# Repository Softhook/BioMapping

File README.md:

# BioMapping 2

*Christian Nold, 2026*

BioMapping 2 records your Galvanic Skin Response — a measure of emotional arousal — mapped to your geographical location as you walk through an environment. 

It has three parts:

- **[The Hardware](#the-hardware)** — a custom skin-response sensor and a GPS wired to a Flipper Zero.
- **[The Firmware](#the-firmware)** — a C application on the Flipper Zero.
- **[The Visualiser](#the-visualiser)** — browser-based analysis and mapping suite.

## The Original Bio Mapping

The first Bio Mapping device (Christian Nold, 2004) was used in workshops with thousands of people across sixteen countries. Participants walked through an area wearing the device and then annotated the recorded data together, producing collective emotion maps. Results from those workshops are published online — the [Greenwich Emotion Map](http://emotionmap.net/), the [San Francisco Emotion Map](http://www.sf.biomapping.net/) and the [Stockport Emotion Map](http://stockport.emotionmap.net/) — and the approach is discussed in the book [*Emotional Cartography*](http://www.emotionalcartography.net/).

## Bio Mapping 2
Unlike most academic research around Galvanic Skin Response, which is bogged down in jargon and caught in cartesian dualism, this project takes a different path. The goal is a system that is technically rigorous while open for everyday community interpretation. While the old Bio Mapping process was great at getting people involved, it didn't provide the insight into what was happening inside the body and the technical rigour and legitimacy to defend the community data. 

Bio Mapping 2 is a high-fidelity successor that takes you much deeper into the body. It uses more sophisticated hardware and software to track nervous system responses and articulate a new vision of the mind-body. This new version aims to give communities a playful and rigorous tool to explore and tackle real-world issues like local planning, environmental stress, and civic change.

## Quick Start

1. **Build the hardware or talk to me** — gather the [components](#components) and follow the [wiring guide](docs/wiring_guide.md).
2. **Flash the app** — download `biomap.fap` from the [Releases](https://github.com/Softhook/BioMapping/releases) page and copy it to your Flipper's SD card, or build from `firmware/` with [`ufbt`](https://pypi.org/project/ufbt/).
3. **Record a walk** — unplug the device from any charger or computer ([why](#electrode-safety)), launch the Bio Mapping app on the Flipper, clip on the electrodes, and walk. Logs save to `/ext/biomapping/*.csv` on the SD card.
4. **Analyse & map** — drop your CSV into the [online visualiser](https://softhook.github.io/BioMapping/visualiser/) — no install needed.

---

# The Hardware

The device is a Flipper Zero running the Bio Mapping app, wired to a custom skin-response sensor circuit and a GPS module. It records to the Flipper's SD card as CSV.

## What It Records

| Stream | Sensor | Notes |
|---|---|---|
| **Galvanic Skin Response (GSR)** | Transimpedance amplifier + 16-bit ADS1115 ADC | Skin conductance in nanosiemens (nS) |
| **Location** | u-blox SAM-M10Q GNSS | About 1.5 m in open sky (datasheet); worse in streets with tall buildings. Up to 10 Hz (GPS + Galileo + GLONASS + BeiDou) |
| **Environmental RF** | Flipper SubGHz radio | Band activity at 815 / 868 / 915 MHz |

Everything is logged to `/ext/biomapping/*.csv` at 10 Hz. A Live Stream mode sends GPS + GSR over Bluetooth instead of recording.

## Hardware Accuracy & Device Comparison

The GSR front-end is built to research-grade specification and measured against a precision metal-film resistor grid (10 kΩ – 9 MΩ), full sweep in [`docs/gsr_sweeps/reference_test_results5.csv`](docs/gsr_sweeps/reference_test_results5.csv).

Accuracy zones by the fraction of real-world track data that falls inside them:

- **≤ ±0.2%** — 10 kΩ – 1 MΩ (1,000 – 100,000 nS): 99.23% of data
- **≤ ±0.5%** — 10 kΩ – 2.2 MΩ (455 – 100,000 nS): 99.74%
- **≤ ±1.0%** — 10 kΩ – 4.7 MΩ (213 – 100,000 nS): 99.84%
- Below 100 nS (over 10 MΩ) the device reports an open circuit (electrodes disconnected / air).

| Device | Type / Price | ADC Resolution | Noise Floor | Accuracy / Error |
| :--- | :--- | :--- | :--- | :--- |
| [BIOPAC EDA100C + MP160](https://www.biopac.com/product/electrodermal-activity-amplifier/) | Lab Benchmark (~£8,000+) | 16-bit *(MP160 DAQ)* | 0.7 nS *(published sensitivity)* | Unknown |
| **[BioMapping 2](https://github.com/Softhook/BioMapping)** | **Custom Portable (~£250)** | **16-bit** *(Onboard ADS1115)* | **2.7 nS** | **±0.2% *(calibrated)* / ±0.4% *(raw)*** |
| [Empatica E4](https://support.empatica.com/hc/en-us/articles/202581999-E4-wristband-technical-specifications) | Clinical Wearable (~£1,350) *(discontinued)* | Not published *(0.9 nS per step)* | Unknown | Unknown |
| [Empatica EmbracePlus](https://www.empatica.com/embraceplus/) | Clinical Research Wearable (~£1,400+) | Not published *(~0.055 nS per step)* | Unknown | Unknown |
| [Shimmer3 GSR+](https://shimmersensing.com/product/shimmer3-gsr-unit/) | Research Wearable (~£650) | 12-bit *(Onboard MCU ADC)* | Unknown | ±3% to ±10% |
| [Movisens EdaMove 4](https://www.movisens.com/en/products/eda-and-activity-sensor/) | Ambulatory Research (~£800+ est.) | 14-bit | Unknown | Unknown |
| [BITalino EDA](https://www.pluxbiosignals.com/collections/bitalino/products/electrodermal-activity-eda-sensor) | Academic Toolkit (~£200) | 10-bit *(BITalino Core)* | Unknown | Unknown |
| [ProtoCentral tinyGSR](https://protocentral.com/product/protocentral-tinygsr-gsr-eda-digital-output-sensor-board-qwiic-stemma-qt/) | Maker Breakout (~£16) | 12-bit | Unknown | Unknown |
| [Grove GSR v1.2](https://wiki.seeedstudio.com/Grove-GSR_Sensor/) | Hobbyist Module (~£12) | Sensor Only | Unknown | Unknown |

> **Note on comparisons:** Most manufacturers don't publish detailed specifications, and the few that do test in different ways, so the numbers above aren't directly comparable. BioMapping's noise floor and accuracy were measured on the bench against precision resistors. ADC resolution is the figure most often published, and it's a rough guide to how carefully a device was built and what it was built for. Where a maker only gives the size of one measurement step (in nS), that is shown in brackets instead.

## Components

**Core boards**
* **[Flipper Zero](https://flipperzero.one/)**
* **SparkFun u-blox SAM-M10Q GNSS Breakout** — GPS positioning. Integrated 15×15 mm ceramic patch antenna, 10 Hz updates.
* **Flipper Zero Prototyping Board** — mounts the ADS1115 and op-amp circuit.
* **ADS1115 Breakout Board** — 16-bit I²C ADC.

**Active components**
* 1× rail-to-rail dual op-amp (MCP602 / MCP6002 / MCP6042 or equivalent 3.3 V CMOS dual op-amp)

**Passive components** (all 0.1% tolerance metal-film resistors)
* 1× 56 kΩ — voltage divider
* 1× 10 kΩ — voltage divider
* 1× 47 kΩ — TIA gain / feedback
* 2× 4.7 kΩ — electrode safety (inline)
* 2× 100 nF (0.1 µF) ceramic capacitors — one power bypass, one feedback filter

**Biometric interface**
* GSR finger electrodes — biometric finger clips, or velcro strips with foil / copper tape.

## Electrode Safety

Only put the electrodes on someone while the device runs on its own battery. Unplug it from chargers, laptops and anything else connected to the mains first. The two 4.7 kΩ resistors limit the current the device itself can send through the skin, but they can't protect against a faulty or leaky charger, whose current could then reach the skin through the electrodes. Being plugged in also adds mains hum to the readings.

## GSR TransImpedance Circuit

The circuit uses both channels of a rail-to-rail dual op-amp: one as a buffered 0.5 V virtual-ground reference (V_ref), and one as a transimpedance amplifier (TIA) that converts skin current to a voltage read differentially by the ADS1115. Two 4.7 kΩ safety resistors protect the electrodes, and a 100 nF feedback capacitor acts as a hardware low-pass filter against 50/60 Hz mains hum.

Full step-by-step pin connections, op-amp pinout, and build phases are in **[`docs/wiring_guide.md`](docs/wiring_guide.md)**.

---

# The Firmware

The onboard firmware (written in C in `firmware/`) runs as an external application (`biomap.fap`) on the Flipper Zero. It acts as an active signal conditioning and synchronization engine, managing the ADC, the GPS module, and the SubGHz radio concurrently.

## What the Firmware Does

- **Real-Time Dynamic Auto-Ranging:** Human skin conductance spans several orders of magnitude across individuals and resting states (from under 500 nS to tens of thousands of nS). The firmware steps the ADS1115's Programmable Gain Amplifier (PGA) across four voltage ranges (from ±2.048 V down to ±0.256 V). A 4 ms settle-gate discards conversion transients during gain switches, and readings from every range are normalised to one common scale, so the output is continuous across gain changes (see the [calibrated wide-range error curve](#hardware-accuracy--device-comparison)).
Looking at other open-source and maker EDA devices whose firmware is available to inspect, almost none implement auto-ranging in firmware.

- **50/60 Hz Mains Hum Rejection:** Ambulatory electrodes pick up AC mains hum from power lines. The ADC uses a background thread to compute a 100 ms boxcar average to null 50 Hz, 60 Hz, and their harmonics (100 Hz, 120 Hz).
- **Multi-Sensor Synchronisation:**  Parses 10 Hz GNSS sentences from the u-blox SAM-M10Q over UART, paces SubGHz RF RSSI snapshots across 815/868/915 MHz without blocking biometric sampling, and streams over Bluetooth or writes to SD.

## Installing the App

A Flipper external app (FAP) for stock firmware; also runs on the API-compatible forks (Momentum, Unleashed, RogueMaster). Download `biomap.fap` from the [Releases](https://github.com/Softhook/BioMapping/releases) page, or build from `firmware/` with [`ufbt`](https://pypi.org/project/ufbt/).

Run the host unit tests with `./run_tests.sh` from `firmware/`.

## CSV Schema

[`docs/csv_schema.md`](docs/csv_schema.md) is the canonical, versioned definition of every column and sentinel value, shared by the device and both visualiser pages.

---

# The Visualiser

The visualiser runs client-side in any modern browser with no server, installation, or build step required. You can launch it directly online:

👉 **[Launch BioMapping Visualiser Online](https://softhook.github.io/BioMapping/visualiser/)**

It provides two entry points:

- **Track Visualiser & Analysis** ([Online App](https://softhook.github.io/BioMapping/visualiser/) | [`visualiser/index.html`](visualiser/index.html)) — Load recorded `.csv` logs from the device to inspect waveforms, clean signals, detect SCR events, map emotional arousal in 2D or 3D, and generate collective emotion maps across participants.
- **Live Stream Visualiser** ([Online Live View](https://softhook.github.io/BioMapping/visualiser/live.html) | [`visualiser/live.html`](visualiser/live.html)) — Connects to the Flipper Zero in real time via Web Bluetooth to graph live biometric arousal and plot GPS movements as you walk. The same view is also built into the main app as the **Live** tab, next to Single and Collective.

## Available Methods & Pipeline

The visualiser provides a full suite of research-grade methods for ambulatory EDA signal processing and spatial analysis:

- **Signal Filtering & Motion Artefact Rejection:**
  - *Hampel / Median Filter* — Removes transient spikes and electrode loose-contact glitches.
  - *Butterworth Low-Pass* — 4th-order zero-phase filter to smooth high-frequency electrical fuzz and tremor.
  - *Zero-Phase Gait Filter* — 4th-order Linkwitz-Riley low-pass at 1.0 Hz, tuned to reject ~1.4–2.0 Hz walking-cadence ripple without ringing or genuine SCR amplitude loss.
- **Tonic / Phasic Decomposition:**
  - *Ultra Low-Pass (EMA)* — Exponential moving average baseline estimation with configurable time window (15–90 s).
  - *Moving Median* — Robust sliding-window baseline estimation.
  - *Trough Tracker* — 10th-percentile baseline follower.
  - *Matching Pursuit Deconvolution* — Greedy decomposition against a canonical Bateman SCRF kernel.
  - *SparsEDA* — Sparse deconvolution using multi-scale dictionary pursuit and active-set refinement.
  - *cvxEDA* — Convex optimisation jointly estimating cubic B-spline tonic drift and physiological sudomotor nerve impulses.
- **Peak Detection (SCR):**
  - *Full-Scan Trough-to-Peak (Default)* — Evaluates candidate peaks against minimum amplitude, SNR, and shape-quality criteria.
  - *Topographic Prominence* — Measures peak height relative to adjacent troughs, isolating compound responses riding larger rises.
  - *Driver Impulses* — Direct peak extraction from deconvolution and cvxEDA sudomotor nerve drivers.
- **Autonomic Indices & Derived Metrics:**
  - *Tonic SCL & Phasic SCR* — Separates slow baseline level from rapid emotional responses.
  - *Peak Density & Phasic AUC* — SCR frequency over time and cumulative phasic energy (Area Under the Curve).
  - *Arousal Index & Tri-Index* — Normalised multi-parameter arousal intensity metrics.
  - *EDASymp* — Spectral sympathetic tone index derived from low-frequency EDA dynamics.
- **Spatial & Collective Mapping:**
  - *Pedestrian GPS Filter Pipeline* — HDOP and fix-type gating, a constant-velocity Kalman filter with a Rauch-Tung-Striebel smoother (holding position while you stand still), optional road snapping, and smooth 10 Hz path reconstruction between fixes. Details in [`docs/gps_filtering_pipeline.md`](docs/gps_filtering_pipeline.md).
  - *Dual 2D/3D Rendering* — Toggle between interactive 2D maps and 3D globe terrain.
  - *Multi-Metric Path Colouring* — Dynamically colour paths by raw GSR, phasic arousal, tonic level, peak density, or RF field activity.
  - *Spatial Hotspots & "Places"* — Spatial clustering of emotional arousal sites along walking routes.
  - *Collective Emotion Topography* — Multi-track aggregation generating shared contour surfaces and arousal isolines across groups of participants.
  - *Environmental Layers* — Overlaid OpenStreetMap geometries (buildings, parks, water), Sentinel-2 NDVI satellite vegetation greenness, and tri-band RF fluid fields.

## Software & Algorithmic Accuracy

Detecting a genuine skin-conductance response (SCR) — separating it from sensor noise, walking motion, and baseline drift — is a well-studied problem in psychophysiology, with two established open-source reference tools: **NeuroKit2** (Python) and **Ledalab** (MATLAB/Octave), plus the peer-reviewed **cvxEDA** convex-optimisation model for decomposing skin conductance into its slow (tonic) and fast (phasic) components.

BioMapping ships its own detection pipeline — built to run entirely client-side, in the browser, on recordings made while walking outdoors — and checks it against those references on three grounds:

1. **A synthetic benchmark with a known answer.** Generated tracks carry SCR events at exactly known times and amplitudes, across a range of difficulty (evenly spaced, densely packed, overlapping bursts, and walking motion), so detection accuracy can be measured directly rather than inferred.
2. **Direct agreement on real recordings.** On clean, stationary recordings — the condition NeuroKit2 and Ledalab are designed for — BioMapping's output is compared peak-for-peak against theirs.
3. **A 62-track real-world field corpus.** Outdoor walking recordings totalling over 100,000 data points, to confirm the above holds up outside the lab.

**On the known-answer synthetic benchmark** (210 injected responses, evenly spaced through overlapping and compound), BioMapping's detectors sit at the strong end of recall, precision, and timing accuracy:

| Detector | Recall | Precision | F1 | Mean timing error |
|---|---:|---:|---:|---:|
| **BioMapping Full-Scan** (production default) | 93.3% | 100.0% | 0.966 | 0.029 s |
| **BioMapping Prominence** | 95.2% | 99.5% | 0.973 | 0.032 s |
| NeuroKit2 (default) | 83.8% | 84.2% | 0.840 | 0.035 s |
| Ledalab CDA (literature-tuned) | 81.9% | 88.2% | 0.849 | 0.556 s |

**On real, clean stationary recordings**, agreement with NeuroKit2 is close to total — BioMapping's Prominence detector matches 100% of NeuroKit2's own peaks (163/163) within ~60 ms, while also picking up dozens of genuine subtle responses NeuroKit2's fixed relative threshold leaves out.

**The standout result is cvxEDA.** BioMapping's from-scratch JavaScript port of the convex-optimisation solver reproduces the published Python reference implementation's output essentially exactly — on the full 62-track field corpus, 99.7% of 4,494 detections matched with a mean timing difference of 0.002 seconds — entirely in-browser, with no Python, MATLAB, or server backend required.

**Where BioMapping is built differently** is ambulatory use: NeuroKit2 and Ledalab are designed for seated laboratory sessions, so BioMapping adds a zero-phase motion filter tuned to footstep cadence and a noise-floor gate for sensor dropouts, neither of which a stationary-recording toolbox needs. On a synthetic walking benchmark with the gait filter enabled, BioMapping recovers 100% of injected responses at 96.8% precision.

 Methodology is in [`docs/eda_benchmark.md`](docs/eda_benchmark.md).

---

# Contributing

Bug reports, hardware build notes, and pull requests are welcome. A few things to know before you submit:

**Firmware (C — `firmware/`)**
- Run the host tests before opening a PR: `./run_tests.sh` from the `firmware/` directory.
- Each device has its own firmware version number: `fap_version` in `firmware/application.fam` (Flipper) and `custom_firmware_version` in `firmware/cardputer/platformio.ini` (Cardputer). Raise it for each release. Every recording's `# Firmware` line carries it, with the git commit it was built from (see [`docs/csv_schema.md`](docs/csv_schema.md)).
- The app targets the Flipper Zero SDK via [`ufbt`](https://pypi.org/project/ufbt/); keep changes compatible with stock firmware and the API-compatible forks (Momentum, Unleashed, RogueMaster).

**Visualiser (JavaScript — `visualiser/`)**
- The app is plain ES modules with no build step. Run `npm ci` once to install dev tools, then:
  - `npm test` — Node test runner
  - `npm run lint` — [Biome](https://biomejs.dev/) linter (also runs on every PR via CI)
  - `npm run lint:deps` — checks module dependencies with [dependency-cruiser](https://github.com/sverweij/dependency-cruiser) (e.g. no circular imports)
  - `npm run typecheck` — [TypeScript](https://www.typescriptlang.org/) checks the JavaScript against its JSDoc comments (`@param`, `@returns`, `@typedef`). Nothing is compiled; the shared data shapes are in `visualiser/types/`
  - `npm run format` — auto-format with Biome
  - `npm run check` — lint, dependency check, type check and tests in one go
- CI runs lint, the dependency check, the type check and tests automatically on every push to `main` and on every pull request.
- Run `git config core.hooksPath .githooks` once per clone to enable a pre-commit hook that auto-formats/lints staged visualiser files with Biome, so CI's lint step doesn't fail on something that could have been caught locally.

**Docs & CSV Schema**
- [`docs/csv_schema.md`](docs/csv_schema.md) is the canonical schema shared by the firmware and both visualiser pages — update it whenever the CSV format changes.
- New `docs/` files for proposals or research notes are welcome.

Open an issue first if you're planning a significant change — especially to the sensor circuit, the signal processing pipeline, or the CSV schema — so we can discuss it before you invest the time.

---

# Licence

Bio Mapping is open for community, artistic, and educational use under the **Bio Mapping Community Licence 1.0**.

In short: You are free to build your own Bio Mapping devices for personal use, research, and workshops (including charging participants for materials). You cannot manufacture or sell Bio Mapping hardware or software commercially without written permission. See [LICENCE.md](LICENCE.md) for full details.

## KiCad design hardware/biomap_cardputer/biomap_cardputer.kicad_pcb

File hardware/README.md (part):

# BioMapping circuit boards (KiCad)

**The focus is the Cardputer board.** All current work goes into it. The Flipper board is not the goal right now and is not being worked on: it is kept, it still builds and passes its checks, but it is not being improved or tested, and it doesn't get the Cardputer board's improvements (for example its C9 is still ceramic, and its GPS pads have no wider solder mask).

Two KiCad 10 projects. Both carry the same GSR circuit as [docs/wiring_guide.md](../docs/wiring_guide.md) and the u-blox SAM-M10Q GPS module, soldered straight onto the board (no breakout board):

| Folder | Plugs into | Board | Power |
|---|---|---|---|
| `biomap_cardputer/` (**the focus**) | A short cable inside the Cardputer, soldered to the EXT socket's legs | 79.8 × 49.8 mm, inside a printed back case ([case/](case/)) | Own 3.3 V regulator (TLV75533), fed from EXT 5 V out |
| `biomap_flipper/` (not being worked on) | Flipper Zero GPIO | 72 × 52 mm, stands up from the Flipper's top edge | Flipper's 3.3 V (pin 9) |

Both boards are placed and routed. KiCad's checks pass on both: the wiring check (ERC) and the design rules check (DRC) show 0 errors and 0 warnings, nothing is unconnected, and each board matches its schematic.

## How the schematic is drawn

Each schematic is one A3 sheet split into labelled blocks:

1. Skin sensor (current-to-voltage amplifier)
2. 0.5 V reference and op-amp supply
3. Analogue-to-digital converter
4. Header (Flipper) or cable socket (Cardputer)
5. GPS
6. 5 V to 3.3 V regulator (Cardputer only)

Inside a block, parts are joined by drawn wires. Between blocks, a signal is carried by a name tag (a "net label"), for example `GSR_SIGNAL` or `I2C_SDA`: every tag with the same name is the same wire. 3.3 V and GND use the usual power symbols.

## How the boards are laid out

Each board has two halves.

- **GSR half.** The parts follow the signal: cuffs, then R3/R4, then the op-amp, then the ADC. The cuff socket sits at the board edge with its opening 0.75 mm inside it, so nothing sticks out past the edge and the plug can be pushed in and pulled out straight, with fingers free to grip it. The amplifier's input wire, which carries the tiny skin current and is the most sensitive to noise, is under 10 mm long (about 7 mm on the Cardputer). Each 100 nF supply capacitor sits close to the power pin of its chip: C1 and C3 about 2 mm (each right beside the pin), C7 about 3.7 mm on the Flipper and 2.5 mm on the Cardputer (bridging the GPS supply pad and the ground pad next to it). The ground ends of C1 and C3 reach ground through a via right beside the capacitor, and the chips' ground pins have their own via within 1.6 mm, so each loop is about 2.3–2.7 mm in all (see `./pcb measure`).
- **0.5 V guard.** A patch of copper held at 0.5 V surrounds the amplifier's input wire, R4, C2, R5 and the cuff-2 wire. That wiring also sits at about 0.5 V, so no current can leak between it and the guard. Without the guard, ground copper 0.3 mm away could leak a little current through flux left on the board, and that current would be added to the skin reading. The flux can't simply be washed off, because the GPS module mustn't be washed. The guard joins the reference at U1 pin 3, right beside the input pin 2. Ground copper is kept out of the guard's area: even U1's own ground pin takes its via just outside it.
- **Test pads.** TP3 (GSR output), TP5 (ground) beside it, and TP4 (0.5 V reference), for a meter or scope when checking a new board. A meter between TP3 and TP4 reads exactly what the ADC reads, so it checks the amplifier without trusting the ADC or the firmware. Expect about 0.50 V from TP4 to TP5. From TP3 to TP4, expect about 0 V with the cuffs unplugged, 0.417 V with 47k in the cuff socket, 0.215 V with 100k and 0.049 V with 470k. A scope on TP3 shows hum before the ADC and the firmware's averaging smooth it. A scope on mains power joins the board to earth, which can change the hum itself; a battery scope doesn't.
- **The test pads can't calibrate the board.** The reading compares the GSR output with the 0.5 V, and the same ADC measures both, so any error in the ADC's own scale cancels out. What sets the accuracy is R5, R3 + R4 and the zero, and the pads come after R3 and R4. The calibration wizard, with resistors in the cuff socket, tests the whole path. If a wizard result looks odd, TP3 shows whether the amplifier or the ADC is off.
- **GPS half.** The module sits in the middle of an unbroken ground area of about 50 × 52 mm (Flipper) or 48 × 50 mm (Cardputer). Small parts sit right beside the pins they serve. C7 bridges the module's supply pin and the ground pin next to it. On the Cardputer the module is turned so its serial pins face up towards the cable socket, its supply pin (VCC) faces the regulator, and its second supply pin (V_IO) and backup pin face the empty space below it. There C6 (10 µF) bridges V_IO and the ground pin next to it, and C8 does the same for the backup pin. The backup cell sits just below the module, beside its charger (D1, R8). Each serial resistor sits at the end that drives its wire: R10 at the GPS (TX), R9 at the cable socket (RX).

On the Flipper, long runs (I2C and the 3.3 V feed) go along the board edge on the other copper layer, outside the GPS area. The Cardputer needs almost none: the cable socket's pins step through to the outer face, and every other track is on it (see "How the Cardputer board is laid out" below). Ground fills both copper layers, joined by a grid of vias: 3 mm apart around the GPS, 5 mm elsewhere, and 2 mm apart under the Cardputer's GPS module. KiCad has a "GPS keep clear" zone that refuses new traces under and around the module, so hand edits can't break this by accident.

## The GPS ground plane

The SAM-M10Q's antenna uses the board's ground as part of the antenna. u-blox's integration manual (in `docs/datasheets/`) asks for:

- a solid ground plane of 50 × 50 mm, with the module in the middle; performance drops a lot below 40 × 40 mm
- no signal traces under the module, and ground vias filling the plane under it
- nothing taller than 3 mm within 10 mm of the module
- a plastic case at least 5 mm from the antenna

SparkFun's breakout is 40.6 × 40.6 mm, the minimum, with ground on both layers and about 100 vias. These boards give the module a larger ground area. The module's own circuit copies SparkFun's:

- 100 nF on the supply (plus a 10 µF reservoir, which SparkFun doesn't have)
- a rechargeable backup cell (BT1, Seiko MS421R, the same cell SparkFun uses), charged through D1 and a 3.3 kΩ resistor (Seiko asks for at least 3 kΩ when charging from 3.3 V), with a capacitor (C8) on the backup pin
- 470 Ω in series with TX and RX

C8 is 100 nF on the Flipper, as on SparkFun's board, and 1 µF on the Cardputer. When the power goes off, the module switches its backup pin over to the cell and draws a short burst of current. u-blox warns that a high resistance on that pin makes the voltage dip. The cell's own resistance is about 600 Ω, so the bigger capacitor gives that burst more to draw on.

On the Cardputer, the solder mask round the module's pads opens 0.05 mm wider than each pad, as in u-blox's footprint drawing. A slightly misplaced mask then can't cover a pad edge, which under the module can't be seen or reached. The Flipper board still has the mask flush with its pads.

Two test pads, SAFEBOOT/PPS and RESET, take the place of SparkFun's header pins. Each has a ground pad 1.2 mm from it (TP6, TP7), so tweezers can bridge the pair and a scope's ground has somewhere to go. Each pad's name is printed beside it. The firmware needs no change: it uses the same serial pins as before.

- **TP1, SAFEBOOT/PPS.** Inside the module, the SAFEBOOT pin is joined to the time pulse output through 1 kΩ (u-blox integration manual, section 3.2.3). The firmware leaves the time pulse at u-blox's default, so once the GPS knows the time, this pad goes high for 0.1 s at the start of every second ("PPS", pulse per second). Before that, and while the GPS sleeps, it stays low. On a scope you see the pulse; on a meter the number jumps once a second. So it shows the GPS has the time without looking at either screen, and it marks the true start of each second for timing tests. Held to ground (TP6) while the GPS powers up, it starts the GPS in safeboot mode. That is almost never needed, because this GPS's own program is fixed in the chip. It also means nothing may pull this pad low at power-up, an LED to ground for example: the GPS would start in safeboot mode and seem dead. A meter or a scope is fine.
- **TP2, RESET.** Bridged to TP7, it resets the GPS. That clears the GPS's stored data, so the next fix is a cold start. It is rarely needed: Options > Cold Reset GPS wipes the same stored data over the serial line, and the firmware never saves settings into the GPS, so turning the power off and on clears any bad setting. It is for a GPS that stops answering even then.
- On the Cardputer these pads face outwards. A metal object lying across a pair would reset the GPS, or start it in safeboot mode at power-up: one more reason to keep metal off this side.

## Parts

- **ADS1115 as a bare chip** (MSOP-10). Both boards have their own I2C pull-up resistors (R6, R7, 4.7 kΩ to the board's 3.3 V). On the Cardputer the ADC has an I2C bus of its own (G3 and G5), and the Cardputer has no pull-ups on those pins.
- **Precision resistors suggested** for R1, R2 and R5 (0.1%), and a **C0G capacitor** for C2. These set the GSR scale directly. R3 and R4, the two 4.7k skin current limiters, are 0.1% too: the firmware subtracts exactly 9.4k for them, and with 1% parts that sum could be up to 94 Ω out, enough to read very sweaty skin (around 10k) up to about 1% low.
- **Op-amp: TI OPA2333AIDR** (U1), a "zero-drift" op-amp. Its input error is under 10 µV, against up to 4.5 mV for the MCP6002 on the hand-built prototype, so the 0.5 V across the skin stays exact and doesn't drift with temperature. It has the same pins as the MCP6002. Buy TI's own part: LCSC also lists cheaper copies from other makers with different specs.
- **C9 (10 µF) across R2** smooths the 0.5 V bias. The bias is taken from 3.3 V, and the GSR reading scales with it, so without C9 any wobble on 3.3 V would show up in the reading. On the Cardputer board C9 is a **tantalum** part (Kyocera AVX TAJP106M010RNJ), with its + end (marked on the board) towards the 0.5 V. Ordinary ceramic capacitors turn knocks into tiny voltages, and anything added to the 0.5 V shows up in the GSR reading; in the case, C9 sits right behind the keyboard and the speaker. Its tiny leakage shifts the 0.5 V very slightly, which the bias check at the start of each recording measures away. The Flipper board's C9 is still ceramic.

Each board's `bom.csv` lists every part with its maker, maker's part number and LCSC number (LCSC is the parts store JLCPCB assembles from). Identical parts share one row. The everyday resistors and capacitors are JLCPCB "basic" parts, which have no extra fitting fee.

Everything is surface-mount and suits machine assembly, except the angled pin headers, and the Cardputer's cable socket, which is on the other face and soldered by hand.

- **Finger cuffs:** JST PH 2-pin side-entry socket, surface-mount (J2, S2B-PH-SM4-TB). Its two side tabs only hold it down. The cuff plug was measured on the prototype's top-entry socket (6 mm wide, pins 2.0 mm apart), so it is JST PH and fits; it is held by the same friction bump in a side-entry socket. JST PH is a common series: spares are easy to buy (LCSC C295747, Digi-Key, Mouser, Farnell), and it is easy to solder by hand (tack one tab, then the two pins, then the other tab).
- **GPS:** u-blox SAM-M10Q-00B (U4), on KiCad's standard SAM-M8Q footprint; u-blox says the two modules are pin-compatible. **LCSC has none in stock**, so buy them from Mouser or Digi-Key and send them to the assembler.
- **Backup cell:** Seiko MS421R-IV03E (rechargeable, 3 V, 1.5 mAh, 4.8 mm). It can go through the soldering oven, so a machine fits it like any other part. It is the cell on SparkFun's SAM-M10Q board, and its footprint (`BioMap.pretty/Seiko_MS421R_IV03E`) copies SparkFun's pads. Those pads match the IV03E terminal drawing on Seiko's MS421R page, with about 0.3 mm to spare: the small corner tab is + (pad 1), the long tab is −. Seiko rates the cell for 3 µA in normal use and 10 µA at most, but with the GPS switched off the module draws 28 µA from it. That doesn't harm the cell, but it gets less of its stored charge out, so expect it to keep satellite data for about a day at most. After a longer time off, the GPS takes longer to find its first position. Not stocked by LCSC; Farnell 3534555.
- **C2** is 1206 size, because 100 nF C0G capacitors are hard to find in 0805.
- **Flipper header:** two angled through-hole pieces, pins 1–8 and 9–18, 17.78 mm apart, to match the gap in the Flipper's GPIO. Through-hole is kept on purpose: these joints hold the board in place.
- **Cardputer connection:** a JST GH 8-pin socket (J1, SM08B-GHS-TB: 1.25 mm pitch, latching, side entry, 4.25 mm tall) on the board's inner face, for a short cable soldered inside the Cardputer (see below). LCSC C265111 (a JLCPCB "extended" part); it is soldered by hand, so it isn't in the factory parts list.

## How the Cardputer board is laid out

Seen from the outside, the GSR circuit is on the left half and the GPS on the right. (In KiCad, which shows the board from the Cardputer's side, it is the other way round.) The board sits inside the printed back case ([case/](case/)), where M5Stack's floor used to be, so it is 2.1 mm smaller than the Cardputer all round. It has the Cardputer's big rounded corners on the EXT edge and smaller rounded corners on the keyboard edge. It has four holes. The case's two long screw posts pass through the big ones (H3, H4), where M5Stack's back screws in, and the board rests on their ledges. Two M2 screws (H1, H2) hold it on two shorter posts.

The cable socket J1 sits on the inner face near the EXT edge, on the GSR side, with its mouth facing into the board. Each of its eight pins drops through a via to the outer face: those 1.6 mm steps are the only tracks on the inner face. From the GPS end, the pins carry the two GPS serial wires, ground, 5 V, SDA, SCL, ground and the ADC's ready line.

- The GPS pair runs left along the top edge, then down to the top of the module as a parallel 45-degree pair, with ground vias between them.
- 5 V runs left under it to the regulator, which sits above the GPS. The regulator's 3.3 V goes out in two branches: down to the GPS, and a spine down the left of the GSR circuit, passing left of the screw post.
- The I2C pair and the ready line go straight down on the other side of the post. The I2C pair turns along the gap between the post and the ADC, then comes down the ADC's left side, where the pull-ups R6 and R7 lie across from the spine. On the way down, both wires step sideways by one resistor's width. So R6 reaches SDA above the step, and R7 reaches SCL below it, with SDA passing between R7's pads.

So no wire crosses another.

The GSR circuit is one block, with the cuff socket on the far short edge from the GPS, its opening 0.75 mm inside the board's edge, behind a window in the case wall. The ADC sits just above the op-amp. The op-amp's output and the 0.5 V reference run straight up to it, side by side, with test pads TP4 (0.5 V) and TP3 (GSR output) on them and TP5 (ground) beside them. The test pads have no printed names, because there is no room: from the GPS side they are 0.5 V, GSR output, ground.

**The ADC's ready line.** The ADS1115's ALERT/RDY pin goes to the cable socket's pin 8, for a wire to EXT pin 3 (G4). That wire isn't fitted yet: G4 is in the middle of the hidden row of legs, and the firmware doesn't use it. With it, the ADC could pulse the line each time a new reading is ready, so the firmware could read exactly 860 readings a second, with none missed and none read twice (see `docs/cardputer_port.md`, "GSR reading speed"). The pin can only pull the line low, so it needs a pull-up resistor. The board has none: the firmware would turn on the ESP32's own pull-up on G4, and switch the ADC's ready mode on (set the top bit of the high threshold register and clear it in the low one). Test pad TP8 (printed RDY) sits on the ready line above the ADC, for a scope or logic analyser, with TP5 as its ground.

## How the Cardputer connects

The board sits in a printed back case that replaces M5Stack's back ([case/README.md](case/README.md)). A short cable joins it to the Cardputer. At one end, its wires are soldered inside the Cardputer onto the legs of the EXT socket. At the other, its plug latches into J1 on the board's inner face. J1 sits in the strip between the EXT edge and the battery, where M5Stack's back had its Lego tubes, so nothing of the Cardputer's comes down that far. Its mouth faces into the board, away from the EXT socket's body, so the plug lies over flat board.

| J1 pin | Signal | EXT leg |
|---|---|---|
| 1 | GPS to Cardputer | G15 |
| 2 | Cardputer to GPS | G13 |
| 3 | Ground | GND |
| 4 | 5 V | 5VO |
| 5 | ADC data (SDA) | G5 |
| 6 | ADC clock (SCL) | G3 |
| 7 | Ground | GND (the same leg) |
| 8 | ADC ready | G4 (no wire yet) |

The pins and their legs are printed on the inner face beside the socket. The inner face also carries `Bio Mapping 2 - Cardputer rev G` (bottom left) and `www.biomapping.net` (bottom right), placed like the credit line and the GPS note on the outer face (JLCPCB prints both faces at no extra cost). The revision letter is set once, as `REV` in `pcbtools/boards/cardputer.py`, and feeds both faces: change it whenever the board changes. The case README explains the soldering inside the Cardputer and the checks before switching on. **5VI must never be connected.**

The firmware uses the same pins (`GSR_SDA_PIN` and `GSR_SCL_PIN` in `firmware/cardputer/src/gsr_cardputer.cpp`). A prototype wired with flywires must follow the board: ADC clock on G3, not G6.

## Check before ordering (both boards)

- **Soldering the GPS module.** Its pads sit underneath it, so it needs an oven or a hotplate. u-blox advises against a hot air gun, which can overheat and damage the module. Follow u-blox's soldering profile and use no-clean flux. Don't wash the board afterwards with water, alcohol or an ultrasonic cleaner; the manual warns that each one can damage the module.
- **Oven limits to give the factory.** You send the GPS modules and backup cells to the factory yourself, so send these limits with them. Every part sits on one face, so one pass through the oven is all the board needs.
  - GPS: one pass only, module facing up, at most 245 °C, with 40–60 s above 217 °C (u-blox integration manual, section 5.3).
  - GPS: keep it in its sealed bag until it is fitted. It soaks up damp from the air (moisture level 4). After about 72 hours out of the bag it has to be baked dry first, or it can crack inside in the oven.
  - Backup cell: two oven passes at most, with the temperature measured on top of the cell (Seiko's catalogue).
- **Which way the antenna faces.** The antenna works best facing the sky. On the Flipper, the board stands up from the top edge, so the antenna faces sideways while the Flipper lies flat and faces up when the Flipper is held upright. On the Cardputer, it faces out from the back.

## Check before ordering (Cardputer)

These come from M5Stack's 3D model and from photos, not from measurements of a real device. `./pcb case` checks the board against the case in 3D (see the case README), and `./pcb print` makes a full-size paper copy to lay on the opened Cardputer (see "Paper fit test" below).

- **Room for the cable socket.** J1 stands 4.25 mm up from the board's inner face, into the strip between the EXT edge and the battery. M5Stack's Lego tubes and add-on screw slots filled that space to within 1 mm of the Cardputer's board, so nothing there should stand taller than 1 mm. Check it on the real Cardputer (case README, measurement 2). With the paper copy laid on, J1 must sit over flat board, clear of the EXT socket's body, the headphone socket and the flat-cable socket beside it.
- **Room for the screw heads.** The heads of the board's two M2 screws (H1, H2) are on the inner face, 1.6 mm tall. Nothing under them on the Cardputer's board may stand taller than about 4.5 mm.
- **The long screws.** Measure M5Stack's back screws first (case README, measurement 1). The case's screw length, and how far each screw reaches into the Cardputer, are settings in `case/cardputer_back.scad`.
- **The ADC clock on G3.** Test 1 in the case README checks it on the prototype.

## Paper fit test (Cardputer)

`./pcb print` writes `out/biomap_cardputer_print.pdf`: the board at full size on one A4 page, seen from outside, inside the Cardputer's own outline.

- Print it at 100% ("Actual size"), not "Fit to page", then measure the two 100 mm rulers on the page. Printers are often slightly off, so check before trusting the fit.
- Cut along the outer line (the Cardputer's outline) and lay it on the opened Cardputer, EXT edge to EXT edge. The two big + marks must sit over the two screw inserts.
- J1 and its pads are on the hidden face, so they are drawn as seen through the paper. They must sit over flat board.
- KiCad draws the page from the board files, so it always matches the current layout. Tracks and copper fill are left out to save ink.

## Factory files

The ways of getting the boards made (UK assembler, JLCPCB, or by hand) and rough costs are in [BUILD_COSTS.md](BUILD_COSTS.md).

`./pcb fab` (or `./pcb fab cardputer`) first runs every check that `./pcb check` runs. If any fails, it writes nothing. Otherwise it fills a folder `out/fab/<board>/` for each board:

| File | What it's for |
|---|---|
| `<board>_gerbers.zip` | Upload this to have the bare board made: one drawing (Gerber file) per layer, plus the drill files |
| `<board>_bom_jlcpcb.csv` | The parts list, in JLCPCB's format |
| `<board>_cpl_jlcpcb.csv` | Where the machine puts each part, in JLCPCB's format |
| `ORDER.txt` | What to choose on the order form, the oven limits, and what to check in the factory's preview |
| `gerbers/` | The zip's contents, to look at in KiCad's GerbView |

- **Part rotation.** JLCPCB counts the angle of a bottom-face part as seen from underneath, and KiCad counts from the top: `./pcb fab` converts this for you. JLCPCB's machines also hold some parts at a different starting angle from KiCad. Their placement preview shows each part on the board: check every chip's pin 1 dot, the diode's stripe and the backup cell's + side. If a part comes out turned, rotate it there, then add its footprint and the angle to `ROTATION_FIX` in `pcbtools/fab.py`, so the next order comes out right without fixing it again.
- **The Cardputer's cable socket** (J1) is on the other face from every other part, so it is left out of the parts list and placement file: solder it by hand.
- The parts list comes from each board's `bom.csv`, which `./pcb build` writes. Bare pads (test pads) and parts soldered by hand are left out.
- `out/` isn't saved in git, so keep a copy of the zip you actually send.

## Tools

Everything is done with one command, `./pcb`, run from this folder. It needs KiCad 10 and nothing else (pictures also need ImageMagick). It runs KiCad's own Python for you. If KiCad isn't in `/Applications`, set `KICAD_APP` to your `KiCad.app`.

```
./pcb --help              list the commands
./pcb <command> --help    details of one command
```

### Where things live

| Path | What it holds |
|---|---|
| `pcbtools/boards/flipper.py`, `cardputer.py` | **The layouts.** Every part's position and every trace, written out by hand. This is what you edit to change a layout. |
| `pcbtools/schematic.py` | The parts lists (which pin joins which net, what to buy) and the schematic drawings. Edit this to change the circuit or the BOM. |
| `pcbtools/rules.py` | Track widths, via size and the 0.15 mm clearance, plus the extra DRC rules written to each board's `.kicad_dru` (below). |
| `pcbtools/limits.py` | Layout limits: how far each decoupling capacitor may be from its chip, how long the GSR wires may be, how many ground vias the GPS needs, how much track may cut the ground plane. |
| `pcbtools/` (the rest) | The machinery: building the board, the checks, measuring, the ground check, pictures, the case. |
| `case/` | The Cardputer's printed back case: the OpenSCAD drawing, `board.scad` (written by `./pcb case`) and the STL files. |
| `biomap_*/` | The KiCad files the tools write. |
| `out/` | Pictures and full check reports. Git ignores it. |

### Changing a layout

1. Look at the parts you want to move: `./pcb parts flipper U1 C1` prints their pad positions, nets and keep-out boxes.
2. Edit their positions or traces in `pcbtools/boards/flipper.py`.
3. Run `./pcb layout flipper`. It rebuilds the board, runs KiCad's design rules check (DRC), tests the layout limits and prints the layout numbers.
4. If DRC finds problems, `./pcb drc flipper` lists each one with the parts and positions involved.
5. `./pcb measure --compare` shows the numbers for the last commit next to yours, so you can see whether the change helped.
6. `./pcb render` draws pictures into `out/` to check by eye.

Units are mm and y points down, as in KiCad. Write tracks with square corners: on the Cardputer board, `BEVEL` at the top of the layout file cuts every square corner at 45 degrees when the board is built (never at a pad or where another track joins). A track can set its own size, or `{"bevel": 0}` to stay square where a cut corner would come too close to a pad. For a part on the back face, `./pcb footprint RF_GPS ublox_SAM-M8Q B 13 17` shows where its pads land at each rotation (back-face parts come out mirrored).

### Commands

| Command | What it does | Changes files? |
|---|---|---|
| `build [board]` | Rebuilds everything: draws the schematics, checks them, lays out the boards, checks the boards. | Yes, all KiCad files |
| `layout [board]` | The quick loop: lays the board out again from the saved schematic, runs DRC, prints the layout numbers. | Yes, the `.kicad_pcb` |
| `check [board]` | Checks the saved files: schematic against the intended connections (two independent ways), KiCad's wiring check (ERC), DRC and the layout limits. | No |
| `drc [board]` | Every DRC problem, with parts and positions. | No |
| `measure [--compare [git-ref]]` | Each decoupling capacitor's distance to its chip's supply *and* ground pin; copper length on the GSR wires and the long wires. | No |
| `ground [--picture] [--break-test]` | The Cardputer board's ground: how far apart the GSR's ground points move when the GPS or the ADC sends current through the ground copper, plus the ground's pieces and the biggest gap between ground vias (see "Ground check" below). Takes a few minutes. | Only `out/` (`--picture`) |
| `parts <board> [REF ...]` | Pad positions, nets and keep-out boxes, as the layout places them. | No |
| `render [board] [--out folder]` | Pictures of the schematic and both faces of each board. | Only `out/` |
| `print [--out file]` | A full-size PDF of the Cardputer board inside the Cardputer's outline, to print and lay on a real Cardputer (see "Paper fit test"). | Only `out/` |
| `case [--no-picture]` | The Cardputer's printed back case: writes `case/board.scad` from the saved board, builds the STL files with OpenSCAD, checks in 3D that the board, its parts and both plugs clear the case, and the GPS's distance to each screw (see [case/README.md](case/README.md)). Needs OpenSCAD. | `case/`, and `out/` for the picture |
| `fab [board]` | The factory files: Gerber and drill zip, JLCPCB parts list and placement file, order notes (see "Factory files"). Runs `check` first and writes nothing if it fails. | Only `out/fab/` |
| `footprint <library> <name> [F\|B] [pad ...]` | Where a footprint's pads land at each rotation. Also reads our own footprints (`BioMap`). | No |
| `eagle <file> [--nets REF ...\|--package NAME]` | Reads Eagle files, such as SparkFun's open designs, without Eagle. This is how the MS421R cell and its pads were found. | No |
| `debug-sch <file>` | When KiCad only says "Failed to load schematic", lists which items it rejects. | No |
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
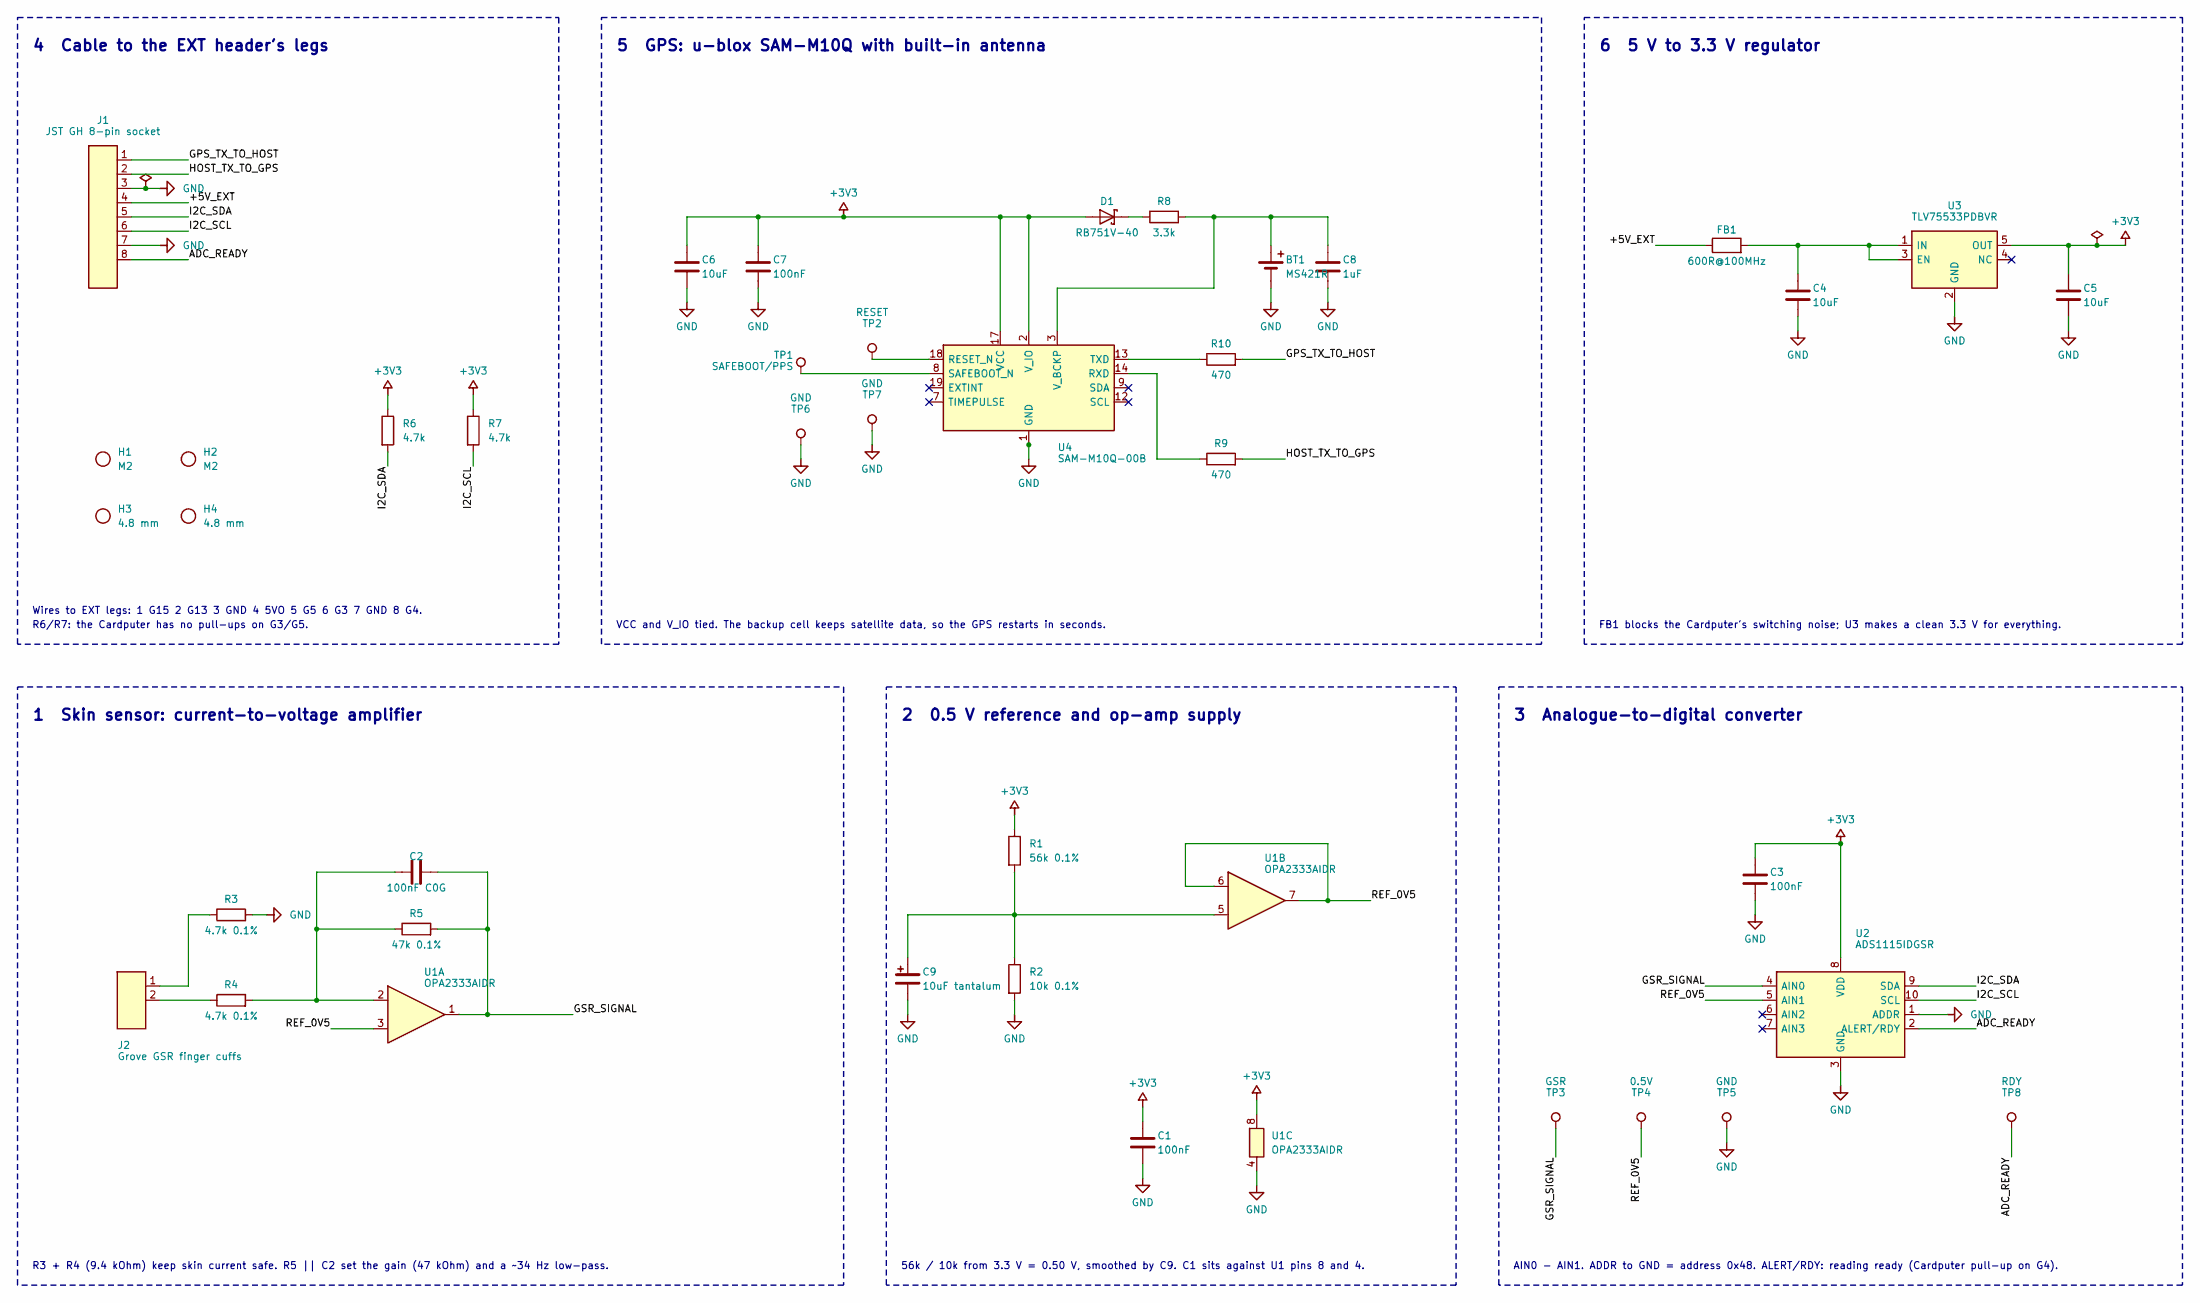
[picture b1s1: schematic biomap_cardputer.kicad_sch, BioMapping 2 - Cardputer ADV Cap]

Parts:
BT1: MS421R; Seiko_MS421R_IV03E; MPN MS421R-IV03E
C1, C3, C7: 100nF; C_0805_2012Metric; MPN CC0805KRX7R9BB104; LCSC C49678
C2: 100nF C0G; C_1206_3216Metric; MPN 1206CG104J500NT; LCSC C46348
C4, C5, C6: 10uF; C_0805_2012Metric; MPN CL21A106KAYNNNE; LCSC C15850
C8: 1uF; C_0805_2012Metric; MPN CL21B105KBFNNNE; LCSC C28323
C9: 10uF tantalum; CP_EIA-2012-15_AVX-P; MPN TAJP106M010RNJ; LCSC C1952866
D1: RB751V-40; D_SOD-323; MPN RB751V-40; LCSC C77353
FB1: 600R@100MHz; L_0805_2012Metric; MPN GZ2012D601TF; LCSC C1017
H1, H2: M2; MountingHole_2.2mm_M2
H3, H4: 4.8 mm; MountingHole_4.8mm
J1: JST GH 8-pin socket; JST_GH_SM08B-GHS-TB_1x08-1MP_P1.25mm_Horizontal; MPN SM08B-GHS-TB(LF)(SN)
J2: Grove GSR finger cuffs; JST_PH_S2B-PH-SM4-TB_1x02-1MP_P2.00mm_Horizontal; MPN S2B-PH-SM4-TB(LF)(SN); LCSC C295747
R1: 56k 0.1%; R_0805_2012Metric; MPN PTFR0805B56K0P9; LCSC C2849276
R2: 10k 0.1%; R_0805_2012Metric; MPN PTFR0805B10K0P9; LCSC C478887
R3, R4: 4.7k 0.1%; R_0805_2012Metric; MPN PTFR0805B4K70P9; LCSC C2849257
R5: 47k 0.1%; R_0805_2012Metric; MPN PTFR0805B47K0P9; LCSC C479101
R6, R7: 4.7k; R_0805_2012Metric; MPN 0805W8F4701T5E; LCSC C17673
R8: 3.3k; R_0805_2012Metric; MPN 0805W8F3301T5E; LCSC C26010
R9, R10: 470; R_0805_2012Metric; MPN 0805W8F4700T5E; LCSC C17710
TP1: SAFEBOOT/PPS; TestPoint_Pad_1.5x1.5mm
TP2: RESET; TestPoint_Pad_1.5x1.5mm
TP3: GSR; TestPoint_Pad_D1.0mm
TP4: 0.5V; TestPoint_Pad_D1.0mm
TP5: GND; TestPoint_Pad_D1.0mm
TP6, TP7: GND; TestPoint_Pad_1.5x1.5mm
TP8: RDY; TestPoint_Pad_D1.0mm
U1: OPA2333AIDR; SOIC-8_3.9x4.9mm_P1.27mm; MPN OPA2333AIDR; LCSC C38732
U2: ADS1115IDGSR; MSOP-10_3x3mm_P0.5mm; MPN ADS1115IDGSR; LCSC C37593
U3: TLV75533PDBVR; SOT-23-5; MPN TLV75533PDBVR; LCSC C404027
U4: SAM-M10Q-00B; ublox_SAM-M8Q; MPN SAM-M10Q-00B

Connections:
+3V3: C1.1, C3.1, C5.1, C6.1, C7.1, D1.2 (A), R1.1, R6.1, R7.1, U1.8 (V+), U2.8 (VDD), U3.5 (OUT), U4.2 (V_IO), U4.17 (VCC)
/+5V_EXT: FB1.1, J1.4
/ADC_READY: J1.8, TP8.1, U2.2 (ALERT/RDY)
/GPS_TX_TO_HOST: J1.1, R10.2
/GSR_SIGNAL: C2.2, R5.2, TP3.1, U1.1, U2.4 (AIN0)
/HOST_TX_TO_GPS: J1.2, R9.2
/I2C_SCL: J1.6, R7.2, U2.10 (SCL)
/I2C_SDA: J1.5, R6.2, U2.9 (SDA)
/REF_0V5: TP4.1, U1.3 (+), U1.6 (-), U1.7, U2.5 (AIN1)
GND: BT1.2 (-), C1.2, C3.2, C4.2, C5.2, C6.2, C7.2, C8.2, C9.2, J1.3, J1.7, R2.2, R3.2, TP5.1, TP6.1, TP7.1, U1.4 (V-), U2.1 (ADDR), U2.3 (GND), U3.2 (GND), U4.1 (GND), U4.4 (GND), U4.5 (GND), U4.6 (GND), U4.10 (GND), U4.11 (GND), U4.15 (GND), U4.16 (GND), U4.20 (GND)
unnamed: BT1.1 (+), C8.1, R8.2, U4.3 (V_BCKP)
unnamed: D1.1 (K), R8.1
unnamed: J2.1, R3.1
unnamed: J2.2, R4.1
unnamed: C2.1, R4.2, R5.1, U1.2 (-)
unnamed: C9.1, R1.2, R2.1, U1.5 (+)
unnamed: C4.1, FB1.2, U3.1 (IN), U3.3 (EN)
unnamed: TP2.1, U4.18 (RESET_N)
unnamed: R9.1, U4.14 (RXD)
unnamed: TP1.1, U4.8 (SAFEBOOT_N)
unnamed: R10.1, U4.13 (TXD)

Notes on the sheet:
1 Skin sensor: current-to-voltage amplifier
R3 + R4 (9.4 kOhm) keep skin current safe. R5 || C2 set the gain (47 kOhm) and a ~34 Hz low-pass.
2 0.5 V reference and op-amp supply
56k / 10k from 3.3 V = 0.50 V, smoothed by C9. C1 sits against U1 pins 8 and 4.
3 Analogue-to-digital converter
AIN0 - AIN1. ADDR to GND = address 0x48. ALERT/RDY: reading ready (Cardputer pull-up on G4).
4 Cable to the EXT header's legs
R6/R7: the Cardputer has no pull-ups on G3/G5.
Wires to EXT legs: 1 G15 2 G13 3 GND 4 5VO 5 G5 6 G3 7 GND 8 G4.
5 GPS: u-blox SAM-M10Q with built-in antenna
VCC and V_IO tied. The backup cell keeps satellite data, so the GPS restarts in seconds.
6 5 V to 3.3 V regulator
FB1 blocks the Cardputer's switching noise; U3 makes a clean 3.3 V for everything.

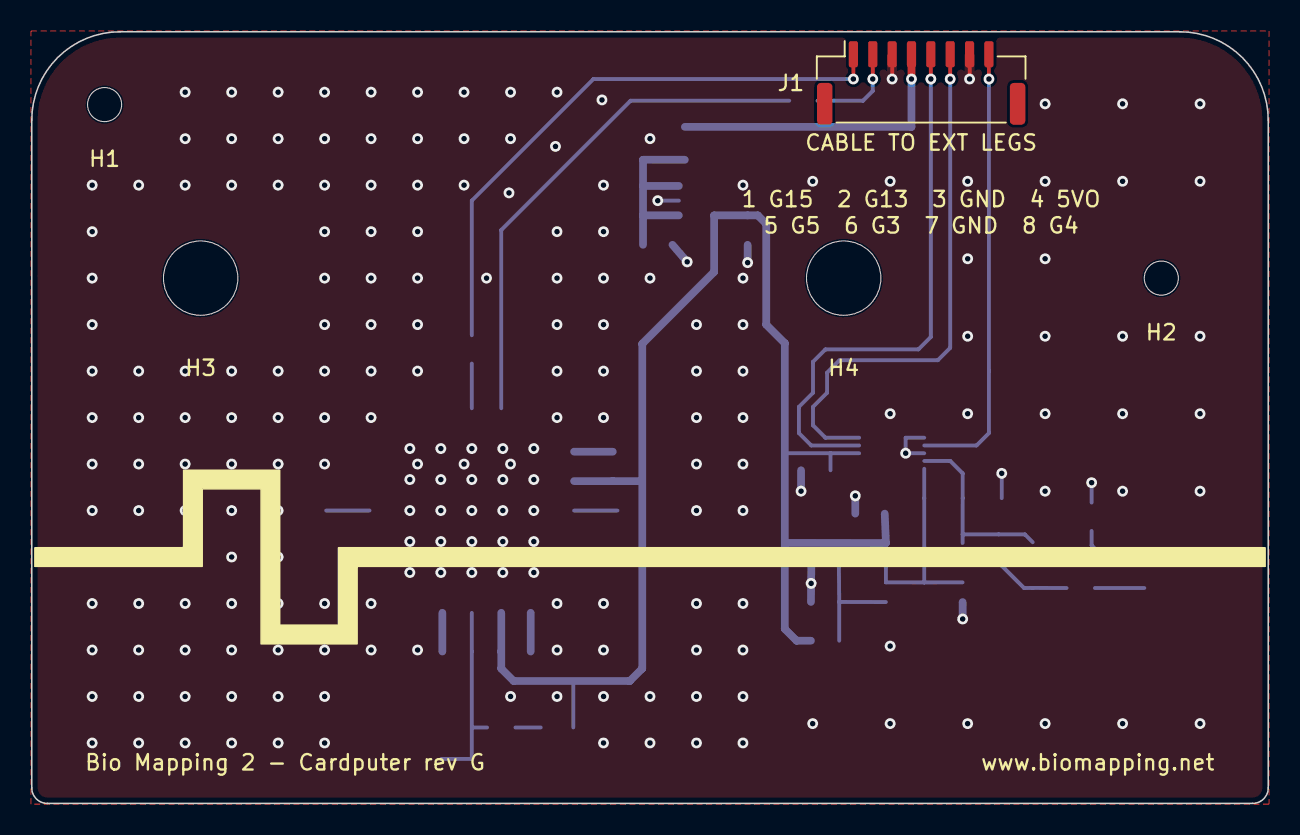
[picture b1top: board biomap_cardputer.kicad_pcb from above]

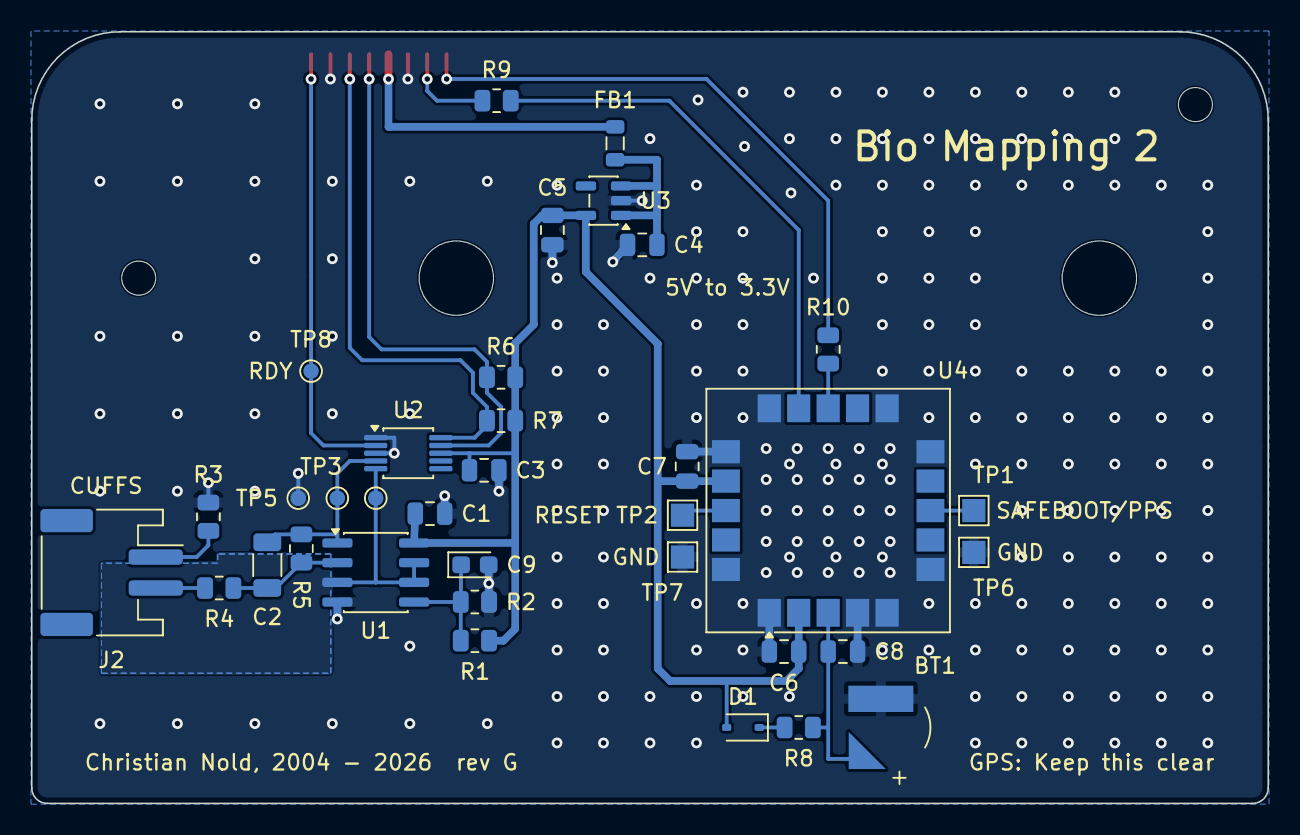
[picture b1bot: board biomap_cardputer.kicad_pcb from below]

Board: 2 copper layers, 79.8 x 49.8 mm, 40 parts (35 on the bottom side), 21 nets.

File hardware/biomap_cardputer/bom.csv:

Designator,Qty,Value,Footprint,Manufacturer,MPN,LCSC,Fit,Note
"BT1",1,"MS421R",Seiko_MS421R_IV03E,"Seiko Instruments","MS421R-IV03E",,SMD,"Rechargeable 3 V 1.5 mAh backup cell, reflow-solderable (as on SparkFun GPS-21834). Rated 10 uA at most; the switched-off GPS draws 28 uA, so it keeps satellite data for about a day at most. Farnell 3534555"
"C1 C3 C7",3,"100nF",C_0805_2012Metric,"YAGEO","CC0805KRX7R9BB104",C49678,SMD,""
"C2",1,"100nF C0G",C_1206_3216Metric,"FH (Guangdong Fenghua)","1206CG104J500NT",C46348,SMD,"TIA filter (~34 Hz). C0G/NP0 only. 1206 size: 100 nF C0G is hard to find in 0805"
"C4 C5 C6",3,"10uF",C_0805_2012Metric,"Samsung","CL21A106KAYNNNE",C15850,SMD,""
"C8",1,"1uF",C_0805_2012Metric,"Samsung","CL21B105KBFNNNE",C28323,SMD,"Backup supply decoupling"
"C9",1,"10uF tantalum",CP_EIA-2012-15_AVX-P,"Kyocera AVX","TAJP106M010RNJ",C1952866,SMD,"Smooths the 0.5 V bias: noise on 3.3 V would otherwise change the GSR gain. Tantalum, + (pad 1) to the 0.5 V: a ceramic one turns knocks into small voltages"
"D1",1,"RB751V-40",D_SOD-323,"Jiangsu Changjing","RB751V-40",C77353,SMD,"Stops the backup cell feeding the 3.3 V rail. Low-leakage type (0.5 uA max): a power Schottky leaks several uA back from the cell, on top of the GPS's own 28 uA"
"FB1",1,"600R@100MHz",L_0805_2012Metric,"Sunlord","GZ2012D601TF",C1017,SMD,"Blocks the Cardputer's boost-converter switching noise"
"J1",1,"JST GH 8-pin socket",JST_GH_SM08B-GHS-TB_1x08-1MP_P1.25mm_Horizontal,"JST","SM08B-GHS-TB(LF)(SN)",,by hand,"Cable socket on the INNER face (towards the Cardputer), soldered by hand. Latching, side entry, 4.25 mm tall. Pin to EXT leg: 1 G15, 2 G13, 3 GND, 4 5VO, 5 G5, 6 G3, 7 GND, 8 G4"
"J2",1,"Grove GSR finger cuffs",JST_PH_S2B-PH-SM4-TB_1x02-1MP_P2.00mm_Horizontal,"JST","S2B-PH-SM4-TB(LF)(SN)",C295747,SMD,"JST PH 2.0 mm side-entry socket for the Grove GSR finger-cuff plug. Surface-mount; the two side tabs only hold it down"
"R1",1,"56k 0.1%",R_0805_2012Metric,"RESI","PTFR0805B56K0P9",C2849276,SMD,"0.5 V bias. Sets the GSR scale. Use 0.1% parts"
"R2",1,"10k 0.1%",R_0805_2012Metric,"RESI","PTFR0805B10K0P9",C478887,SMD,"0.5 V bias. Sets the GSR scale. Use 0.1% parts"
"R3 R4",2,"4.7k 0.1%",R_0805_2012Metric,"RESI","PTFR0805B4K70P9",C2849257,SMD,"Skin current limit. The firmware subtracts R3 + R4 = 9.4k: use 0.1% parts"
"R5",1,"47k 0.1%",R_0805_2012Metric,"RESI","PTFR0805B47K0P9",C479101,SMD,"TIA gain. Sets the GSR scale. Use 0.1% parts"
"R6 R7",2,"4.7k",R_0805_2012Metric,"UNI-ROYAL","0805W8F4701T5E",C17673,SMD,""
"R8",1,"3.3k",R_0805_2012Metric,"UNI-ROYAL","0805W8F3301T5E",C26010,SMD,"Backup cell charge current limit"
"R9 R10",2,"470",R_0805_2012Metric,"UNI-ROYAL","0805W8F4700T5E",C17710,SMD,""
"TP1",1,"SAFEBOOT/PPS",TestPoint_Pad_1.5x1.5mm,"","",,bare pad,"Also the GPS time pulse: joined inside the module to TIMEPULSE through 1k, so once the GPS has the time it goes high for 0.1 s at the start of each second. Short to TP6 (GND) at power-up for safeboot mode. Nothing may pull it low at power-up"
"TP2",1,"RESET",TestPoint_Pad_1.5x1.5mm,"","",,bare pad,"Short to TP7 (GND) to reset the GPS. Clears its stored data: the next fix is a cold start"
"TP3",1,"GSR",TestPoint_Pad_D1.0mm,"","",,bare pad,"Test pad: amplifier output"
"TP4",1,"0.5V",TestPoint_Pad_D1.0mm,"","",,bare pad,"Test pad: 0.5 V reference"
"TP5",1,"GND",TestPoint_Pad_D1.0mm,"","",,bare pad,"Test pad: ground, for the meter or scope"
"TP6 TP7",2,"GND",TestPoint_Pad_1.5x1.5mm,"","",,bare pad,"Ground beside TP1 (TP6) and TP2 (TP7): tweezers across the pair, or a scope's ground"
"TP8",1,"RDY",TestPoint_Pad_D1.0mm,"","",,bare pad,"Test pad: ADC reading-ready pulses (860 a second), for a scope or logic analyser"
"U1",1,"OPA2333AIDR",SOIC-8_3.9x4.9mm_P1.27mm,"Texas Instruments","OPA2333AIDR",C38732,SMD,"Zero-drift op-amp: offset under 10 uV, so the 0.5 V across the skin stays exact. Same pins as the MCP6002 on the prototype"
"U2",1,"ADS1115IDGSR",MSOP-10_3x3mm_P0.5mm,"Texas Instruments","ADS1115IDGSR",C37593,SMD,"I2C address 0x48 (ADDR to GND)"
"U3",1,"TLV75533PDBVR",SOT-23-5,"Texas Instruments","TLV75533PDBVR",C404027,SMD,"5 V to 3.3 V regulator (LDO), 500 mA, 1% accuracy, low noise"
"U4",1,"SAM-M10Q-00B",ublox_SAM-M8Q,"u-blox","SAM-M10Q-00B",,SMD,"GPS with built-in patch antenna. Pin-compatible with the SAM-M8Q footprint. Needs the ground plane around it. LCSC has none: buy from Mouser or Digi-Key and send to the assembler"
